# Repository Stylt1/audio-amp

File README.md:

View this project on [CADLAB.io](https://cadlab.io/project/30509). 

# 🎵 AudioAMP V1

This project features a 4-layer Class-D stereo audio amplifier based on **PAM8610** IC, delivering up to **2x 10W** output power.

---

## 📑 Table of Contents
- [✨ Key Features](#-key-features)
- [🛠️ Hardware Specifications](#️-hardware-specifications)
- [🧩 System Block Diagram](#-system-block-diagram)
- [📂 Repository Structure](#-repository-structure)
- [📸 Gallery & Schematics](#-gallery--schematics)

---

## ✨ Key Features

- **Amplification:** **PAM8610** (Class-D) stereo amplifier providing **2x 10W** output power.
- **4-Layer PCB Stackup:** 4-layer board design with dedicated power and ground planes:
  - **F.Cu (Top):** Signal + GND fill
  - **In1.Cu (Inner 1):** GND fill
  - **In2.Cu (Inner 2):** Power
  - **B.Cu (Bottom):** Secondary signal + GND fill
- **Supply Voltage Range:** from **9V to 12V DC** via standard DC05 DC Barrel Jack.
- **Volume & Power Control:** **10K logarithmic potentiometer** with an ON/OFF switch.
- **Connections:** 3.5 mm AUX stereo input jack and screw terminal blocks for Left (L) and Right (R) speakers.
- **Clean sound:** Bulk **2200 µF** electrolytic decoupling capacitor on power supply lines + LC output filters (33µH inductors) for ripple noise reduction and high signal fidelity.

---

## 🛠️ Hardware Specs

| Parameter | Specification |
| :--- | :--- |
| **Amplifier IC** | PAM8610 (Class-D Stereo) |
| **Output Power** | 10W + 10W RMS (into 8Ω @ 12V DC) |
| **Supply Voltage** | 9V – 12V DC |
| **PCB Stackup** | 4-Layer FR4 (Top, In1 [GND], In2 [PWR], Bottom) |
| **Power Connector** | 5.5 x 2.1 mm DC Barrel Jack |
| **Audio Input** | 3.5 mm Stereo AUX Jack |
| **Speaker Outputs** | Screw Terminal Blocks (Left & Right) |
| **Potentiometer** | 10K Logarithmic with ON/OFF Switch |
| **Filtration** | 2200 µF Bulk Electrolytic Cap + Output LC Filters |

---

## 🧩 System Block Diagram

---

## 📦 Production & Manufacturing Files

All production files required for manufacturing and PCBA assembly are located in the `production/` directory or under [GitHub Releases](../../releases):

---

## 📂 Repository Structure

```text
AudioAMP-V1/
├── hardware/              # KiCad project source files (.kicad_pro, .kicad_sch, .kicad_pcb)
├── img/                   # Documentation graphics, 3D renders, and layer views
├── production/            # Manufacturing deliverables
│   ├── bom/               # Bill of Materials (CSV)
│   ├── gerbers/           # 4-Layer Gerber files (ZIP archive)
│   └── schematics/        # Schematic diagram (PDF)
├── LICENSE.txt            # License
└── README.md              # Main project documentation
```

---

## 📸 Gallery & Schematics

### 3D Render
| Top View | Angled View |
|:---:|:---:|
| | |

### 4-Layer PCB Layout

| Top Layer (F.Cu) | Inner Layer 1 (In1.Cu - GND) |
|:---:|:---:|
| | |

| Inner Layer 2 (In2.Cu - PWR) | Bottom Layer (B.Cu) |
|:---:|:---:|
| | |

### Schematic Diagram

---

## 📝 License & Author

- **Designer:** Stylt
- **License:** ([CC BY-NC-ND 4.0 License](LICENSE))

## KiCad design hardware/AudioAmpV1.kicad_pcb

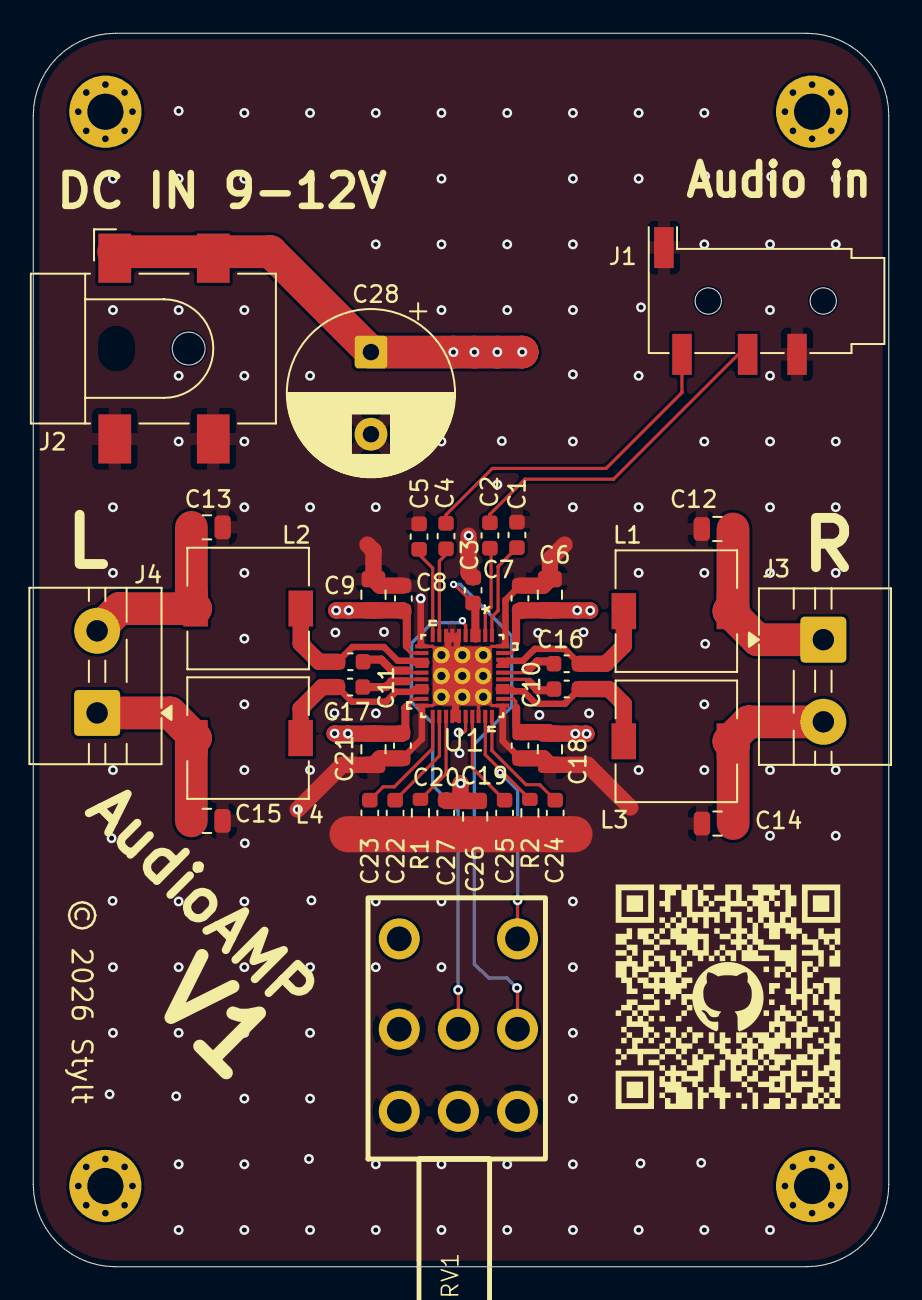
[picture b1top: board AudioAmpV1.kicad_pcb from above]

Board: 4 copper layers, 52.1 x 75.1 mm, 40 parts (0 on the bottom side), 28 nets.

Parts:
C1, C2, C3, C4, C5, C7, C8, C10, C11, C16, C17, C19, C20, C23, C24, C25: 1uF; C_0603_1608Metric
C6, C9, C18, C21, C26: 10uF; C_0805_2012Metric
C12, C13, C14, C15: 0,47uF; C_0805_2012Metric
C22: 220pF; C_0603_1608Metric
C27: 100nF; C_0603_1608Metric
C28: 2200uF; CP_Radial_D10.0mm_P5.00mm
J1: 3,5mm Jack; Jack_3.5mm_KoreanHropartsElec_PJ-320D-4A_Horizontal
J2: Barrel_Jack_Switch; BarrelJack_CLIFF_FC681465S_SMT_Horizontal
J3: Speaker_R; TerminalBlock_MaiXu_MX126-5.0-02P_1x02_P5.00mm
J4: Speaker_L; TerminalBlock_MaiXu_MX126-5.0-02P_1x02_P5.00mm
L1, L2, L3, L4: 33uH/22uH, 2A; L_7.3x7.3_H4.5
R1: 120K; R_0603_1608Metric
R2: 100K; R_0603_1608Metric
RV1: 10K LOG; AudioPot
U1: PAM8610; QFN40-40P-POWER

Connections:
/schematic/+12V: C6.2, C7.2, C8.2, C9.2, C18.2, C19.2, C20.2, C21.2, C26.2, C27.2, C28.1, J2.1, RV1.SW1, U1.12 (PVCCL), U1.19 (PVCCL1), U1.26 (AVCC), U1.32 (PVCCR), U1.39 (PVCCR1)
/schematic/LINP: C4.1, J1.T
/schematic/RINP: C2.1, J1.R
/schematic/SWITCH2: R2.1, RV1.SW2, U1.29 (/SD)
GND: C1.1, C3.1, C5.1, C6.1, C7.1, C8.1, C9.1, C12.2, C13.2, C14.2, C15.2, C18.1, C19.1, C20.1, C21.1, C22.2, C23.2, C24.2, C25.2, C26.1, C27.1, C28.2, J1.S, J2.2, J2.3, R1.2, R2.2, RV1.3, RV1.MP (MountPin), U1.6 (REFGND), U1.7 (AGND1), U1.8 (/FADE), U1.11 (PGNDL), U1.20 (PGNDL1), U1.24 (AGND), U1.25 (MUTE), U1.28 (AGND2), U1.31 (PGNDR), U1.40 (PGNDR1), U1.41 (PAD), U1.42 (PAD1), U1.GND (HOLE1), U1.GND1 (HOLE2), U1.GND2 (HOLE3), U1.GND3 (HOLE4), U1.GND4 (HOLE5), U1.GND5 (HOLE6), U1.GND6 (HOLE7), U1.GND7 (HOLE8), U1.GND8 (HOLE9)
unnamed: C12.1, J3.1, L1.1
unnamed: C14.1, J3.2, L3.1
unnamed: C15.1, J4.1, L4.2
unnamed: C13.1, J4.2, L2.2
unnamed: C3.2, RV1.1, U1.3 (AVDD), U1.4 (VREF)
unnamed: C11.2, U1.15 (BSLN)
unnamed: C17.1, U1.16 (BSLP)
unnamed: C10.2, U1.36 (BSRN)
unnamed: C16.1, U1.35 (BSRP)
unnamed: C22.1, U1.22 (COSC)
unnamed: C5.2, U1.10 (LINN)
unnamed: C4.2, U1.9 (LINP)
unnamed: C11.1, L2.1, U1.13 (LOUTN), U1.14 (LOUTN1)
unnamed: C17.2, L4.1, U1.17 (LOUTP1), U1.18 (LOUTP)
unnamed: C1.2, U1.1 (RINN)
unnamed: C2.2, U1.2 (RINP)
unnamed: R1.1, U1.23 (ROSC)
unnamed: C10.1, L1.2, U1.37 (ROUTN1), U1.38 (ROUTN)
unnamed: C16.2, L3.2, U1.33 (ROUTP), U1.34 (ROUTP1)
unnamed: C25.1, U1.27 (V2P5)
unnamed: C23.1, U1.21 (VCLAMPL)
unnamed: C24.1, U1.30 (VCLAMPR)
unnamed: RV1.2, U1.5 (VOLUME)

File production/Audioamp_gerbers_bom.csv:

Designator,Footprint,Quantity,Value,LCSC Part #
"C1, C10, C11, C16, C17, C19, C2, C20, C23, C24, C25, C3, C4, C5, C7, C8",0603,16,1uF,
"C12, C13, C14, C15",0805,4,"0,47uF",
"C18, C21, C26, C6, C9",0805,5,10uF,
C22,0603,1,220pF,
C27,0603,1,100nF,
C28,CP_Radial_D10.0mm_P5.00mm,1,2200uF,
J1,Jack_3.5mm_KoreanHropartsElec_PJ-320D-4A_Horizontal,1,"3,5mm Jack",
J2,BarrelJack_CLIFF_FC681465S_SMT_Horizontal,1,Barrel_Jack_Switch,
J3,TerminalBlock_MaiXu_MX126-5.0-02P_1x02_P5.00mm,1,Speaker_R,
J4,TerminalBlock_MaiXu_MX126-5.0-02P_1x02_P5.00mm,1,Speaker_L,
"L1, L2, L3, L4",L_7.3x7.3_H4.5,4,"33uH/22uH, 2A",
R1,0603,1,120K,
R2,0603,1,100K,
RV1,AudioPot,1,10K LOG,
U1,QFN40-40P-POWER,1,PAM8610,

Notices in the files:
hardware/AudioAmpV1.kicad_pcb:
© 2026 Stylt
